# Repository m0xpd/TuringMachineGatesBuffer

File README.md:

# Turing Machine Gates Buffer
This repository contains design details for an add-on circuit, which buffers signals from the GATES Expander port of [Music Thing Modular](https://www.musicthing.co.uk/)'s [Turing Machine](https://www.musicthing.co.uk/Turing-Machine/) random looping sequencer.

This buffer circuit was developed in response to my own requirement to obtain reliable output voltages from the Turing Machine's GATES expander port, 
particularly when using the [Voltages expander](https://www.musicthing.co.uk/Turing-Voltages-Expander/) under my ['Tuning Strategy'](https://github.com/m0xpd/TuningStrategyForVoltages), 
where small voltage errors immediately cause noticeable tuning problems.

The buffer requires no modifications to the Turing Machine - it plugs onto the GATES and Power headers, which it replaces. There is an option to add a spacer 
and an M3 screw down to one of the tapped spacers on the Turing Machine for mechanical stability, which is strongly recommended.

# Background

I had noticed a tendency for the voltages produced at the GATES output of the Turing Machine to droop when a large number of bits were activated in 
the 'gate' sequence. This problem was exacerbated when the [PULSES expander](https://www.musicthing.co.uk/Turing-Pulse-Expander/) was used. 
The Turing Machine's power line '+12V_BACK' was observed to droop by over 1V under such loading conditions (*when no such change was seen on the system 
power supply*), making the fall in the GATEx output voltages less surprising (although the 78L09 regulated supply to the CD4050's *should* have prevented 
this - see below).

Designing a buffer for the GATE outputs under these conditions required that the additional circuit did not rely on the either the board's 12V supply or the 
magnitude of the GATEx signals. 

Although a number of design options were possible, I chose to use CD4066 "Analog Switches" (which are inexpensive and familiar to the synth DIY community) 
controlled by the GATE signals, to switch a steady voltage to the GATES expander port.

In the Turing Machine design, the GATE signals are at 9V (the supply Voltage provided to the 4050 "Buffers"). I decided to drop this to 5V i) to give more clear 
air between the failing supply and the voltage level and ii) because it is consistent with the needs of my [tuning strategy](https://github.com/m0xpd/TuningStrategyForVoltages) (where I already set the SCALE control on VOLTAGES quite low). I couln't go much lower, because I still wanted the LEDs on VOLTAGES to light up with no modifications.

Here's my schematic (click for a full-size version):

There are .sch and .brd files (developed in EAGLE) for the printed circuit board in the [PCB folder](https://github.com/m0xpd/TuringMachineGatesBuffer/tree/main/PCB), along with a BoM (in EAGLE's usual format).

# Specifications

The buffer adds an additional 14 mm of depth to the Turing Machine, making the Turing Machine & Buffer extend 50 mm behind the front panel when a standard power 
header is inserted into the buffer's power receptacle (55mm if the power cable's IDC header has a strain relief fitted).

The buffer draws 2mA of current from the +12V rail and nothing from the 5V or -12V rails. 

# License

This design is published under a [Creative Commons BY-SA 4.0](https://github.com/m0xpd/TuringMachineGatesBuffer/blob/main/LICENSE.txt) License.

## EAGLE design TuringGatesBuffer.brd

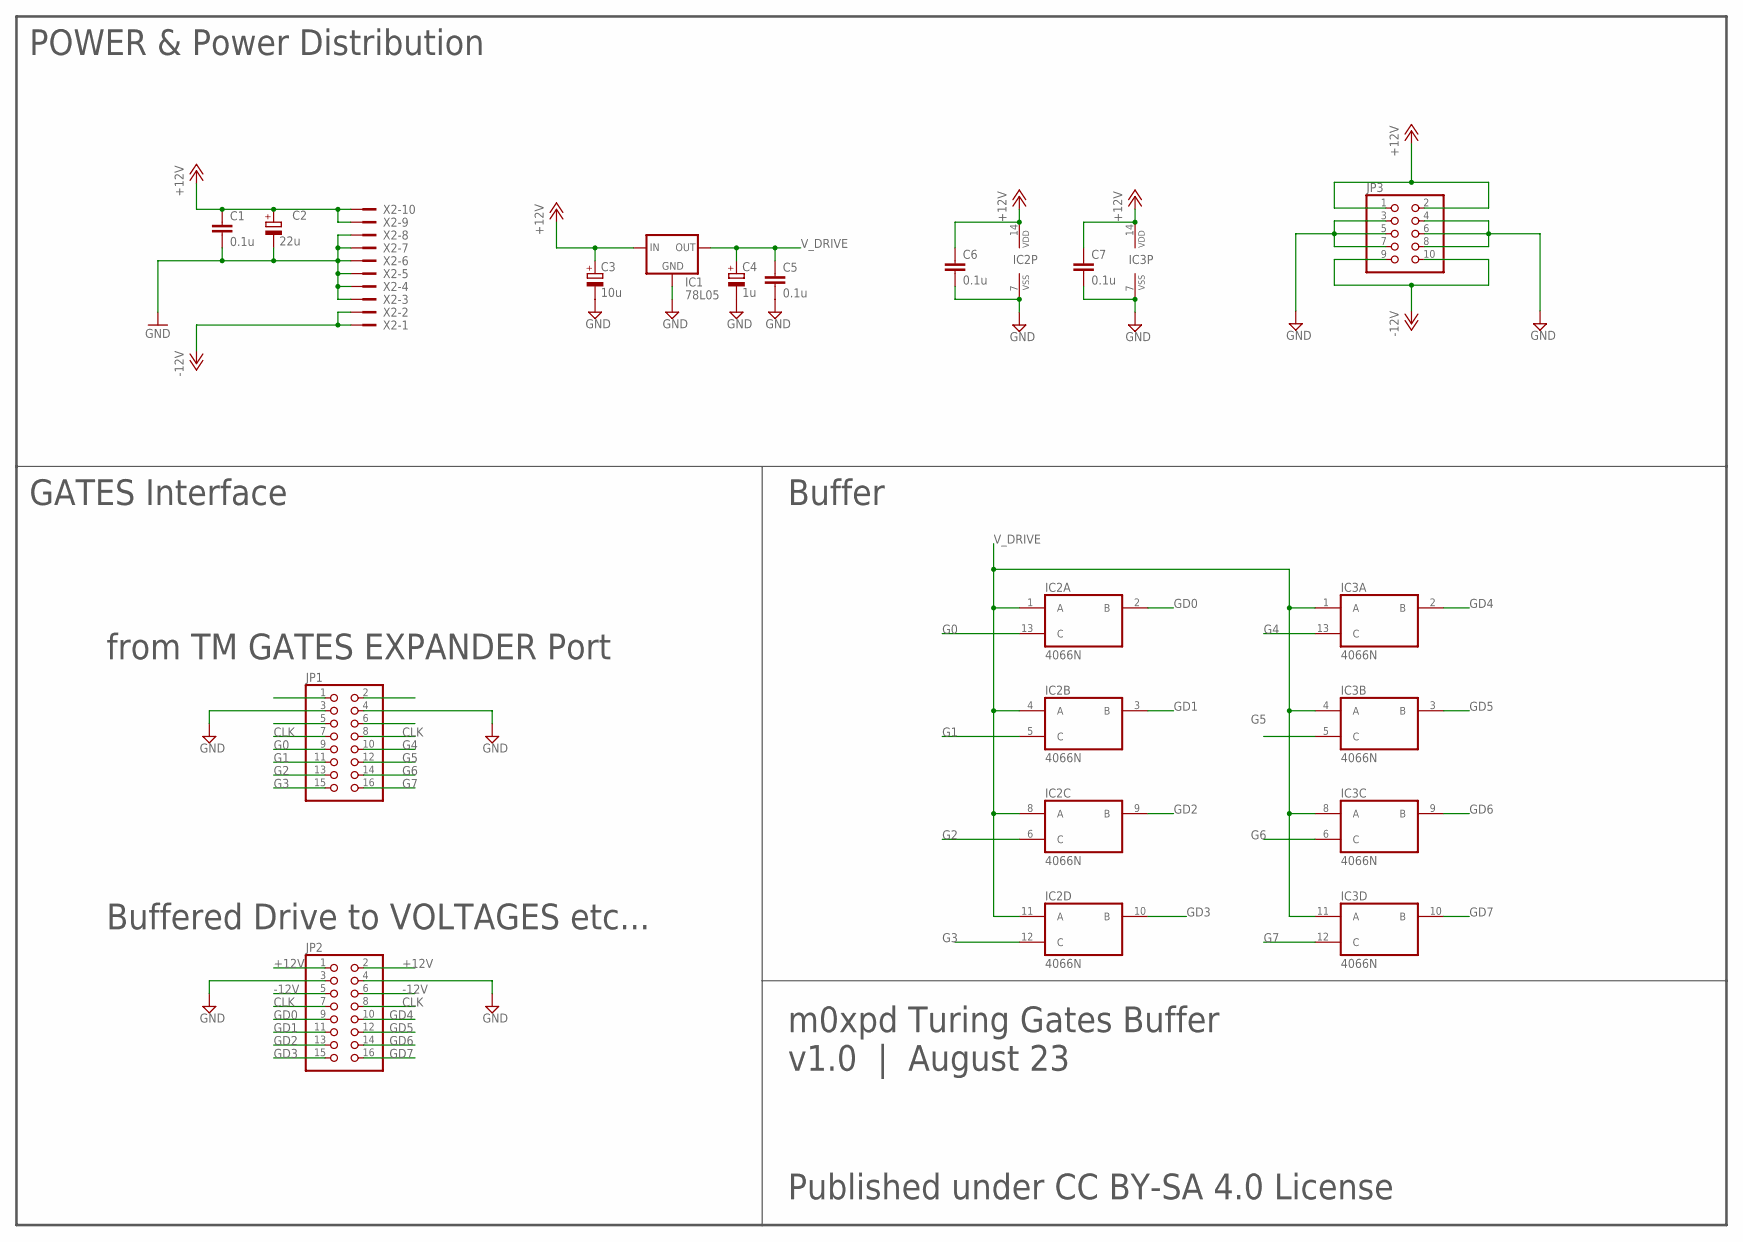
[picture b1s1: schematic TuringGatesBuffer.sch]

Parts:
C1, C5, C6, C7: 0.1u; C050-025X075
C2: 22u; E2,5-5
C3: 10u; E2,5-5
C4: 1u; E2,5-5
IC1: 78L05; 78LXX
IC2, IC3: 4066N; DIL14
JP1, JP2: PINHD-2X8; 2X08
JP3: PINHD-2X5; 2X05
X2: 2510-; PAK100/2500-10

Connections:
+12V: C1.1, C2.+, C3.+, C6.1, C7.1, IC1.IN, IC2.14 (VDD), IC3.14 (VDD), JP2.1, JP2.2, JP3.1, JP3.2, X2.9, X2.10
-12V: JP2.5, JP2.6, JP3.9, JP3.10, X2.1, X2.2
CLK: JP1.7, JP1.8, JP2.7, JP2.8
G0: IC2.13 (C), JP1.9
G1: IC2.5 (C), JP1.11
G2: IC2.6 (C), JP1.13
G3: IC2.12 (C), JP1.15
G4: IC3.13 (C), JP1.10
G5: IC3.5 (C), JP1.12
G6: IC3.6 (C), JP1.14
G7: IC3.12 (C), JP1.16
GD0: IC2.2 (B), JP2.9
GD1: IC2.3 (B), JP2.11
GD2: IC2.9 (B), JP2.13
GD3: IC2.10 (B), JP2.15
GD4: IC3.2 (B), JP2.10
GD5: IC3.3 (B), JP2.12
GD6: IC3.9 (B), JP2.14
GD7: IC3.10 (B), JP2.16
GND: C1.2, C2.-, C3.-, C4.-, C5.2, C6.2, C7.2, IC1.GND, IC2.7 (VSS), IC3.7 (VSS), JP1.3, JP1.4, JP2.3, JP2.4, JP3.3, JP3.4, JP3.5, JP3.6, JP3.7, JP3.8, X2.3, X2.4, X2.5, X2.6, X2.7, X2.8
V_DRIVE: C4.+, C5.1, IC1.OUT, IC2.1 (A), IC2.4 (A), IC2.8 (A), IC2.11 (A), IC3.1 (A), IC3.4 (A), IC3.8 (A), IC3.11 (A)

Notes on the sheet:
m0xpd Turing Gates Buffer
v1.0 | August 23
Published under CC BY-SA 4.0 License
Buffer
GATES Interface
POWER & Power Distribution
from TM GATES EXPANDER Port
Buffered Drive to VOLTAGES etc...

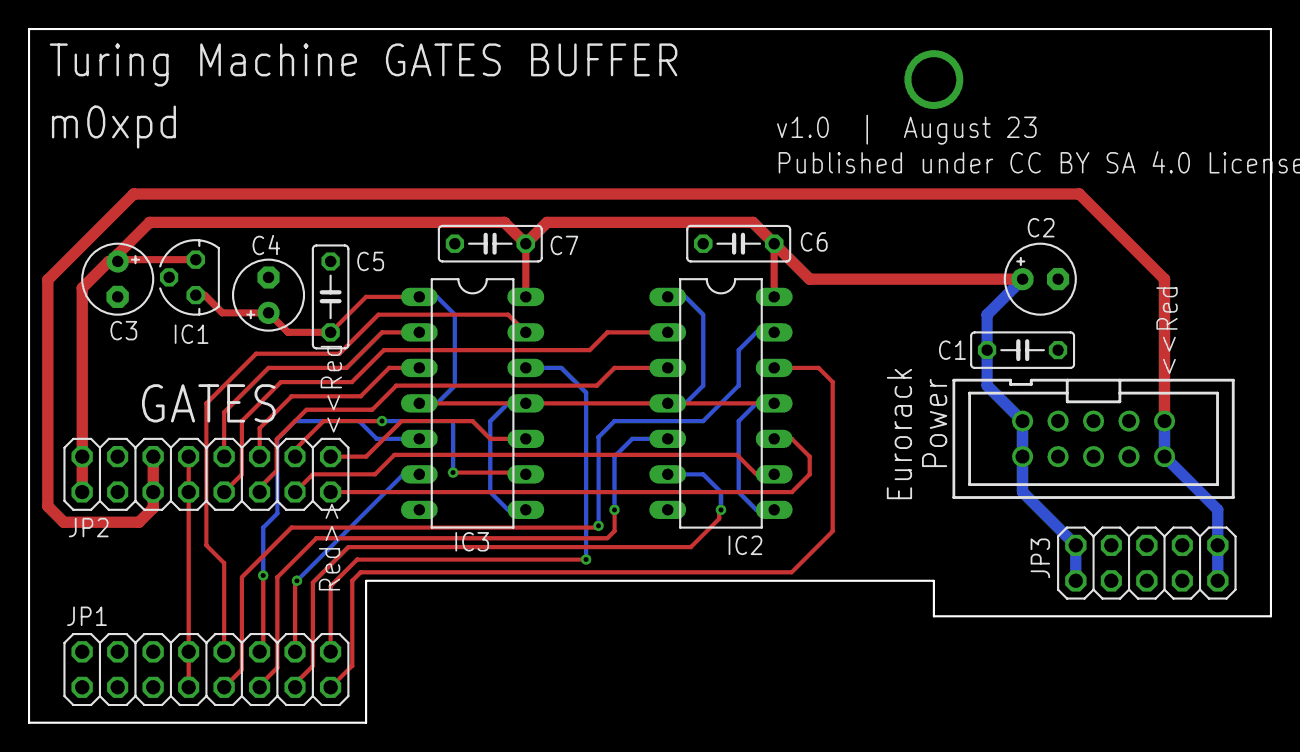
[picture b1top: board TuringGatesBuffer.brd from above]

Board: 2 copper layers, 88.9 x 49.7 mm, 14 parts (0 on the bottom side), 21 nets.

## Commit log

2023-08-26 Rename TuringGatesBuffer.sch to PCB/TuringGatesBuffer.sch
2023-08-26 Rename TuringGatesBuffer.brd to PCB/TuringGatesBuffer.brd
